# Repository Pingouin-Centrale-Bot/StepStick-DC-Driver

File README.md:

# StepStick DC Driver V2
A dual DC/H-bridge driver, designed as a drop-in replacement for a standard stepstick.  
Can drive two DC motors, or be used as four independent half-bridges.  
Designed around the `TB67H453FNG` IC. Datasheets can be found [here](Components/TB67H453FNG/).

## Specs
- Dual H-Bridge : Can drive two DC loads in both directions, or four DC loads unidirectionally
- 3.3A Max per channel
- Accepts an input power voltage from 4.5v to 44v
- Based around a 4 layer PCB, to improve heat dissipation (a heat sink and active cooling is highly recommended)
- The maximum intensity can be configured with the trimmer, by adjusting Vref
- Can be enabled or disabled with the `en` pin, just like a standard stepstick
- Compatible with both 5v and 3.3v logic voltage (If using 5v to power VCC, you must adjust the trimmer so that Vref stays below 3.3v!)

## Pinout

You can use the `Pololu_Breakout_A4988` symbol from the default KiCad library, with its accompanying default footprint. Here is a pinout correspondence for the pins :

| StepStick DC Driver | Pololu A4988 |
|:-------------------:|:------------:|
|         OB1         |      1B      |
|         OB2         |      1A      |
|         OA2         |      2A      |
|         OA1         |      2B      |
|         IA2         |      DIR     |
|         IA1         |     STEP     |
|         IB2         |     RESET    |
|         IB1         |      MS3     |
|         MSB         |      MS2     |
|         MSA         |      MS1     |
|         VCC         |      VDD     |
|          NC         |     SLEEP    |

> [!WARNING]
> You need to add a 100uf capacitor between the `VM` and `GND` pins.

## Configuration
If the resistors on the BOM are respected, the maximum intensity per channel can be configured by setting the `Vref` voltage :  
Imax(A)=Vref(v)
The driver will regulate the intensity to prevent it from getting higher.

The configuration is common to both H-bridge.

## Control
Channel A and B are both controlled by their own two pins `Ix1` and `Ix2`.  
They are 3 ways to control the outputs, configured respectively by `MSx` :

| MSx |       Mode       |
|:---:|:----------------:|
|  L  |    Phase/Enable control         |
|  H  |  PWM control                    |
| Hi-z/Open| Individual half bridge control |

### Phase/Enable control (MSx=Low)

| Ix1 | Ix2 | Ox1 | Ox2 |       Mode       |
|:---:|:---:|:---:|:---:|:----------------:|
|  L  | L/H |  L  |  L  |    Short Brake   |
|  H  |  L  |  L  |  H  |     Reverse      |
|  H  |  H  |  H  |  L  |     Forward      |

### PWM control (MSx=High)

| Ix1 | Ix2 | Ox1 | Ox2 |       Mode       |
|:---:|:---:|:---:|:---:|:----------------:|
|  L  |  L  |  Hi-Z  |  Hi-Z  |    Coast   |
|  L  |  H  |  L  |  H  |     Reverse      |
|  H  |  L  |  H  |  L  |     Forward      |
|  H  |  H  |  L  |  L  |     Short brake      |

### Individual half bridge control (MSx=Hi-z/Open)

| Ixx | Oxx |       Mode       |
|:---:|:---:|:----------------:|
|  L  |  L  |    Short Brake   |
|  H  |  H  |     Reverse      |

> [!NOTE]
> Current limiting does not work in half bridge mode, so beware of currents!

### All

If left open, a pin will be pulled down (considered L).
If you do not want to use one of the channels, you can simply not connect the output to anything.

## Fabrication notes
The constraints have been set up for Aisler's Beautiful Boards service.  
It is advised to use a .8mm total thickness instead of the standard 1.6mm to improve the thermal dissipation.

## Real world testing
### Issues found
- Silkscreen is inverted between IAx and IBx
- The enable logic is reversed to what it should be if trying to emulate a stepstick

### Notes
When an overcurrent event happens, the driver deactivates for 25us. In the event of a short circuit, this means the driver will be off most of the time, and so the measured intensity (mean intensity) will be very low, and so the driver cannot be used to regulate current.

### Power dissipation
No overheating was found when used at .8A on one channel. Further testing is necessary.

# StepStick DC Driver V1
See [here](/V1/).

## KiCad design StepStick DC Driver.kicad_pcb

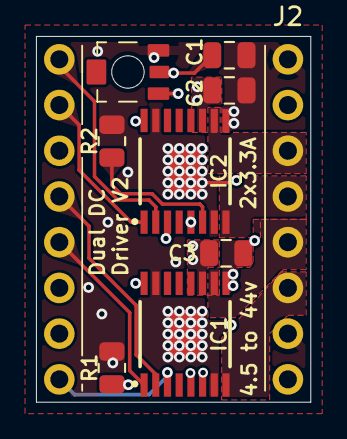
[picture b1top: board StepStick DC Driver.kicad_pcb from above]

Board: 4 copper layers, 15.2 x 20.3 mm, 10 parts (0 on the bottom side), 17 nets.

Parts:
C1, C2, C3: 1u; C_0805_2012Metric
IC1, IC2: TB67H453FNG
J1, J2: Conn_01x08_Pin; PinHeader_1x08_P2.54mm_Vertical
R1, R2: 1k; R_0805_2012Metric
RV1: R_Potentiometer_Trim 100k; POT_EVM3R

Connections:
/DIR: IC2.2 (PH/IN2_), J1.1
/EN: IC1.3 (NSLEEP), IC2.3 (NSLEEP), J1.8
/MS1: IC1.16 (PMODE), J1.7
/MS2: IC2.16 (PMODE), J1.6
/MS3: IC1.1 (EN/IN1_), J1.5
/OA1: IC1.8 (OUT1), J2.6
/OA2: IC1.10 (OUT2), J2.5
/OB1: IC2.10 (OUT2), J2.3
/OB2: IC2.8 (OUT1), J2.4
/RESET: IC1.2 (PH/IN2_), J1.4
/STEP: IC2.1 (EN/IN1_), J1.2
/VCC: J2.2, RV1.1
/VMOT: C2.2, C3.2, IC1.11 (VM), IC2.11 (VM), J2.8
/VREF: C1.1, IC1.5 (VREF), IC2.5 (VREF), RV1.2
GND: C1.2, C2.1, C3.1, IC1.7 (IMODE), IC1.9 (PGND), IC1.15 (GND), IC1.17 (EP), IC2.7 (IMODE), IC2.9 (PGND), IC2.15 (GND), IC2.17 (EP), J2.1, J2.7, R1.1, R2.1, RV1.3
unnamed: IC1.6 (ISENSE), R1.2
unnamed: IC2.6 (ISENSE), R2.2

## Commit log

2026-03-18 Added CERN Open Hardware Licence Version 2 - Weakly Reciprocal
2026-03-18 Added symbol guidance, and corrected spelling
2026-03-21 V2 Driver created, Moved V1 to subfolder
2026-05-01 Update README with testing notes
